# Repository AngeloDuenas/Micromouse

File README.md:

# Micromouse Robot Control PCB

A custom two-layer printed circuit board for a Micromouse robot, developed in KiCad. The hardware integrates an STM32-based controller, infrared wall sensing, dual DC motor control, encoder connections, and battery-powered voltage regulation for autonomous maze-navigation development.

This repository documents the electrical design and PCB implementation. Hardware validation and robot navigation performance are not claimed by the design files alone.

## Hardware Overview

| Subsystem | Implementation | Function |
| --- | --- | --- |
| Microcontroller | STM32F411RE on NUCLEO-F411RE | Central control and peripheral interfaces |
| Motor driver | L293D dual H-bridge | Drives two DC gearmotors |
| Motor feedback | Two 6-pin motor/encoder connectors | Interfaces to the gearmotor encoders |
| Wall sensing | 4 x INL-5AMIR15 IR emitters and 4 x SFH 313 FA receivers | Detects nearby maze walls |
| IR switching | 4 x BS170 MOSFETs | Controls the IR emitters |
| Voltage regulation | TPS62162DSG buck converter | Generates the 3.3 V supply rail |
| Power input | 2-pin battery connector and 500SSP1S2M2QEA switch | Connects and switches battery power |
| Debug interface | 4-pin SWD connector | Provides programming/debug signal access |

## System Block Diagram

```mermaid
flowchart TB
    BAT["Battery Input"] --> SW["Power Switch"]
    SW --> VBAT["Battery Supply (VBAT)"]
    VBAT --> REG["TPS62162DSG Buck Converter"]
    REG --> V33["3.3 V Supply"]
    V33 --> MCU["NUCLEO-F411RE / STM32F411RE"]
    V33 --> IR["4 Infrared Emitter / Receiver Channels"]
    VBAT --> DRV["L293D Dual H-Bridge"]
    MCU -->|"Motor control signals"| DRV
    DRV -->|"Motor output"| LEFT["Left DC Gearmotor"]
    DRV -->|"Motor output"| RIGHT["Right DC Gearmotor"]
    LEFT -->|"Encoder feedback"| MCU
    RIGHT -->|"Encoder feedback"| MCU
    MCU -->|"Emitter control"| IR
    IR -->|"Wall sensing feedback"| MCU
    SWD["SWD / Reset Header"] --- MCU
```

The battery rail supplies the motor driver and the buck regulator. The regulated 3.3 V rail serves the microcontroller and infrared sensing circuitry. The STM32 controls the two motors and receives encoder and infrared sensor signals for closed-loop navigation.

## Hardware Design

### Microcontroller and Debugging

The design uses an **ST NUCLEO-F411RE** board built around the **STM32F411RE** microcontroller. The controller interfaces with the wall sensors, motor driver, and motor encoders. A separate header exposes SWD and reset-related signals for debugging.

### Drive System

An **L293D** dual H-bridge controls two DC gearmotors. Each motor connects through a 6-pin interface that also accommodates encoder signals. The motor power path uses the battery supply, while control and feedback signals connect to the STM32.

### Infrared Wall Detection

Four sensing channels provide wall-detection inputs. Each channel combines an **INL-5AMIR15** infrared emitter, an **SFH 313 FA** infrared receiver, and a **BS170** MOSFET-based emitter control circuit. The microcontroller controls illumination and reads the corresponding sensor outputs.

### Power Distribution

A two-pin battery connector and mechanical power switch feed the **VBAT** net. The **TPS62162DSG** buck converter produces the **3.3 V** supply for the low-voltage electronics. Battery, regulator, and motor-driver requirements must be checked against the selected battery and motor operating conditions before assembly.

## PCB and Design Files

The PCB is designed as a **two-layer board** in **KiCad**. The project includes hierarchical schematic sheets, a PCB layout, imported component libraries and 3D models, a bill of materials, and existing fabrication outputs.

```text
.
├── team3_micromouse_202526_7F5.kicad_pro
├── team3_micromouse_202526_7F5.kicad_sch
├── team3_micromouse_202526_7F5.kicad_pcb
├── Microcontroller.kicad_sch
├── motors.kicad_sch
├── IR.kicad_sch
├── power_module.kicad_sch
├── team3_BOM_micromouse_202526_7F5.xlsx
├── imports/
├── gerber/
└── README.md
```

The `imports/` directory contains third-party symbols, footprints, and mechanical models. The `gerber/` directory contains previously generated fabrication files and should not be assumed to represent the latest schematic revision.

## Opening the Project

1. Install **KiCad 9** or a version compatible with the project files.
2. Open `team3_micromouse_202526_7F5.kicad_pro` in KiCad.
3. Review the hierarchical schematic and the PCB layout.
4. Resolve any local symbol, footprint, or 3D-model library paths if prompted.
5. Run electrical rules checking (ERC) and design rules checking (DRC) before generating new production files.

## Development Status

**Hardware design in progress.** The supplied archive contains PCB and schematic design files, but does not establish a completed, assembled, or validated robot. The schematic sheets have been revised more recently than the existing PCB and fabrication outputs; review their consistency before ordering boards.

Current engineering checks include supply-voltage compatibility, motor-driver and switch current ratings, regulator loading, encoder and sensor pin assignments, and board-level ERC/DRC results. Firmware and measured test results are not included in the supplied hardware archive.

## Project Attribution

Maintained by **Angelo Duenas**. Original design credits are retained in the schematic title blocks.

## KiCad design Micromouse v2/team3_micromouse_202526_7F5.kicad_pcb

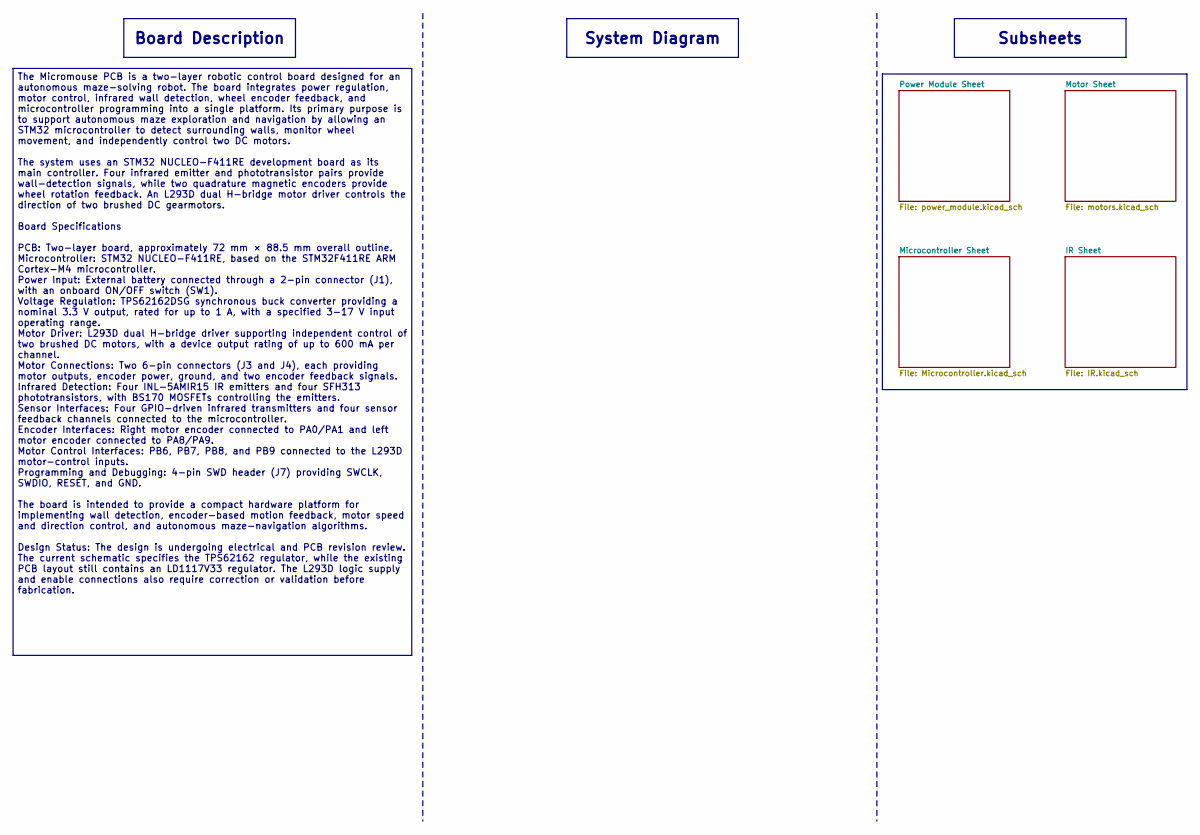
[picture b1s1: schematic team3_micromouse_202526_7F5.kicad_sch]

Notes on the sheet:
System Diagram
Board Description
The Micromouse PCB is a two-layer robotic control board designed for an autonomous maze-solving robot. The board integrates power regulation, motor control, infrared wall detection, wheel encoder feedback, and microcontroller programming into a single platform. Its primary purpose is to support aut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
Subsheets

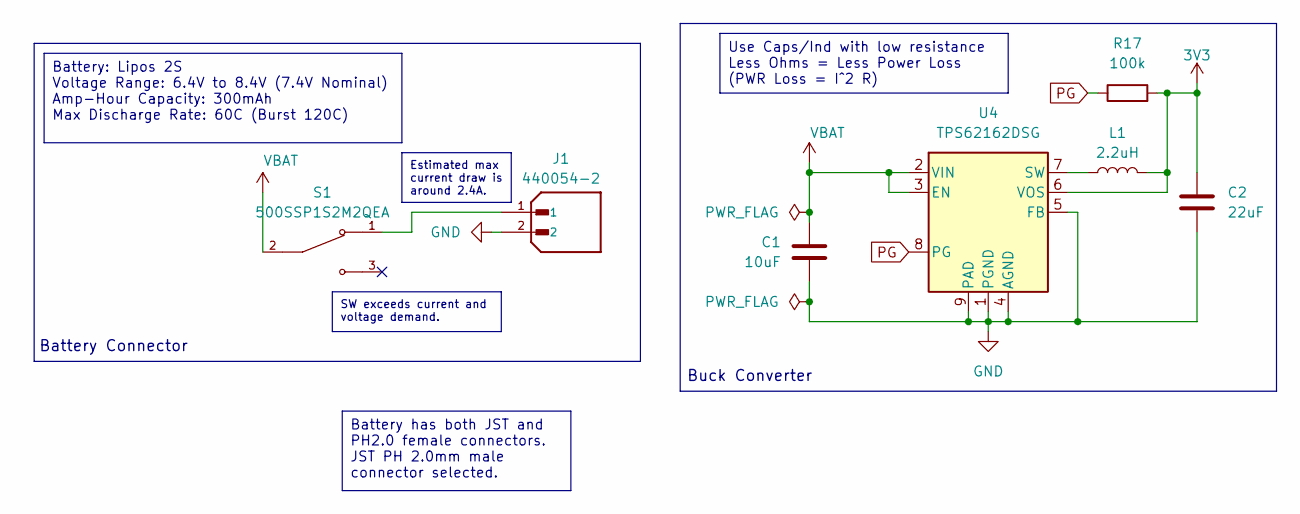
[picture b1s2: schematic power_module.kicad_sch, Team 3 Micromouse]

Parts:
C1: 10uF; CAP_C320_KEM
C2: 22uF; CAP_C320_KEM
J1: 440054-2; TE_440054-2_1x02_P2.00mm_Vertical; PARTREV F9
L1: 2.2uH; L_0603_1608Metric
R17: 100k; R_0603_1608Metric
S1: 500SSP1S2M2QEA; SW_500SSP1S2M2QEA; PARTREV C
U4: TPS62162DSG; WSON-8-1EP_2x2mm_P0.5mm_EP0.9x1.6mm_ThermalVias

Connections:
3V3: C2.1, L1.2, R17.2, U4.6 (VOS); also elsewhere on the board
GND: C1.2, C2.2, J1.2, U4.1 (PGND), U4.4 (AGND), U4.5 (FB), U4.9 (PAD); also elsewhere on the board
unnamed: J1.1, S1.1
unnamed: L1.1, U4.7 (SW)
PG: R17.1, U4.8 (PG)
VBAT: C1.1, S1.2, U4.2 (VIN), U4.3 (EN); also elsewhere on the board

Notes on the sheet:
Battery Connector
Buck Converter
Estimated max current draw is around 2.4A.
Use Caps/Ind with low resistance Less Ohms = Less Power Loss (PWR Loss = I^2 R)
Battery has both JST and PH2.0 female connectors. JST PH 2.0mm male connector selected.
SW exceeds current and voltage demand.
Battery: Lipos 2S Voltage Range: 6.4V to 8.4V (7.4V Nominal) Amp-Hour Capacity: 300mAh Max Discharge Rate: 60C (Burst 120C)

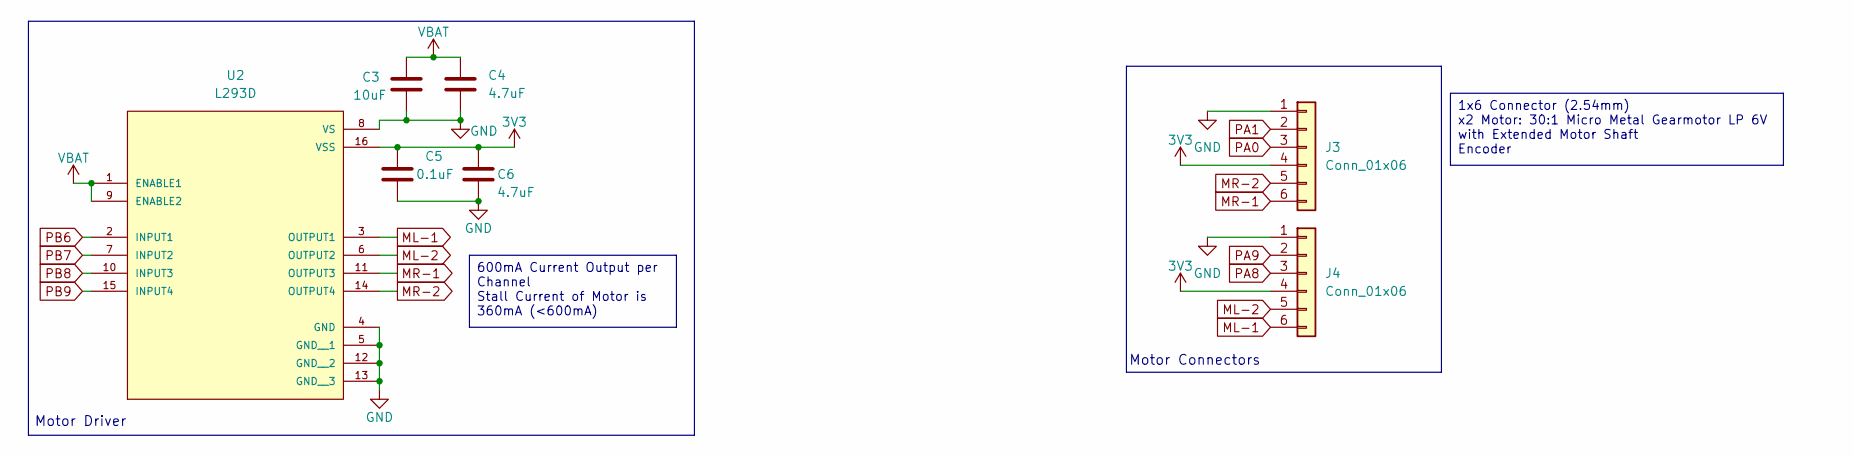
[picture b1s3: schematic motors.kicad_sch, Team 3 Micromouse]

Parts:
C3: 10uF; CAP_C320_KEM
C4, C6: 4.7uF; CAP_C320_KEM
C5: 0.1uF; CAP_C320_KEM
J3, J4: Conn_01x06; PinHeader_1x06_P2.54mm_Vertical
U2: L293D; DIP880W50P254L2000H510Q16

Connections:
3V3: C5.1, C6.1, J3.4, J4.4, U2.16 (VSS); also elsewhere on the board
GND: C3.2, C4.2, C5.2, C6.2, J3.1, J4.1, U2.4 (GND), U2.5 (GND__1), U2.8 (VS), U2.12 (GND__2), U2.13 (GND__3); also elsewhere on the board
ML-1: J4.6, U2.3 (OUTPUT1)
ML-2: J4.5, U2.6 (OUTPUT2)
MR-1: J3.6, U2.11 (OUTPUT3)
MR-2: J3.5, U2.14 (OUTPUT4)
PA0: J3.3; also elsewhere on the board
PA1: J3.2; also elsewhere on the board
PA8: J4.3; also elsewhere on the board
PA9: J4.2; also elsewhere on the board
PB6: U2.2 (INPUT1); also elsewhere on the board
PB7: U2.7 (INPUT2); also elsewhere on the board
PB8: U2.10 (INPUT3); also elsewhere on the board
PB9: U2.15 (INPUT4); also elsewhere on the board
VBAT: C3.1, C4.1, U2.1 (ENABLE1), U2.9 (ENABLE2); also elsewhere on the board

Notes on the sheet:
Motor Connectors
Motor Driver
1x6 Connector (2.54mm) x2 Motor: 30:1 Micro Metal Gearmotor LP 6V with Extended Motor Shaft Encoder
600mA Current Output per Channel Stall Current of Motor is 360mA (<600mA)

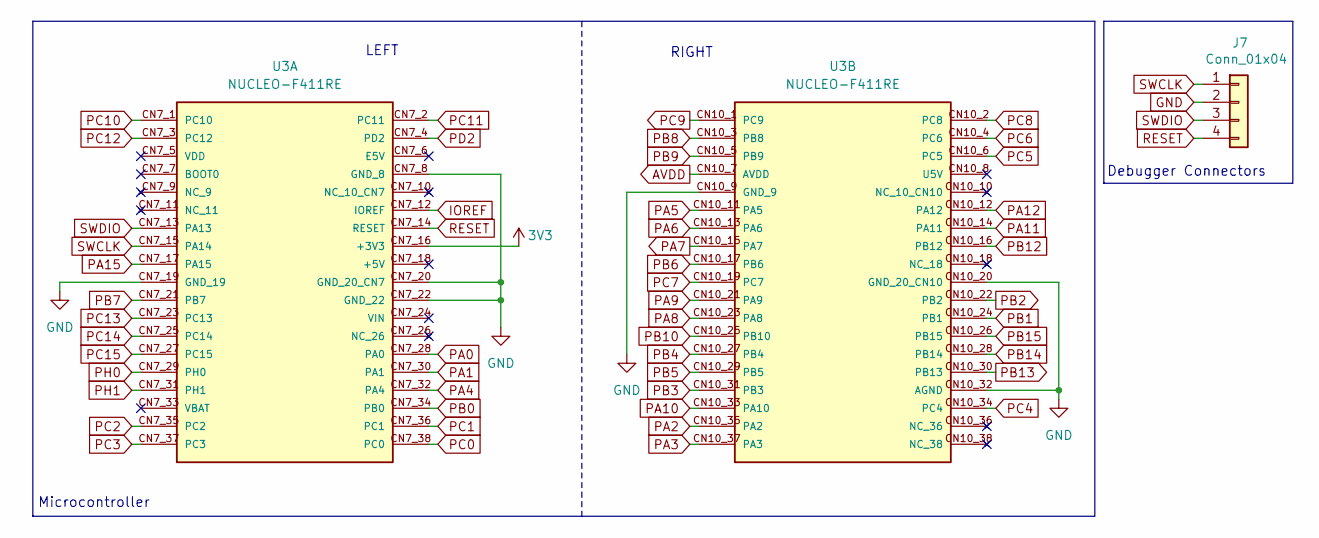
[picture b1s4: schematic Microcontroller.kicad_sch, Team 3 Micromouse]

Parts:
J7: Conn_01x04; PinSocket_1x04_P2.54mm_Vertical
U3: NUCLEO-F411RE; PARTREV 14; DigiKey_Part_Number 497-14711-ND

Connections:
3V3: U3.CN7_16 (+3V3); also elsewhere on the board
AVDD: U3.CN10_7 (AVDD)
GND: J7.2, U3.CN7_8 (GND_8), U3.CN7_19 (GND_19), U3.CN7_20 (GND_20_CN7), U3.CN7_22 (GND_22), U3.CN10_9 (GND_9), U3.CN10_20 (GND_20_CN10), U3.CN10_32 (AGND); also elsewhere on the board
IOREF: U3.CN7_12 (IOREF)
PA0: U3.CN7_28 (PA0); also elsewhere on the board
PA1: U3.CN7_30 (PA1); also elsewhere on the board
PA2: U3.CN10_35 (PA2)
PA3: U3.CN10_37 (PA3)
PA4: U3.CN7_32 (PA4)
PA5: U3.CN10_11 (PA5)
PA6: U3.CN10_13 (PA6); also elsewhere on the board
PA7: U3.CN10_15 (PA7); also elsewhere on the board
PA8: U3.CN10_23 (PA8); also elsewhere on the board
PA9: U3.CN10_21 (PA9); also elsewhere on the board
PA10: U3.CN10_33 (PA10)
PA11: U3.CN10_14 (PA11)
PA12: U3.CN10_12 (PA12)
PA15: U3.CN7_17 (PA15)
PB0: U3.CN7_34 (PB0)
PB1: U3.CN10_24 (PB1); also elsewhere on the board
PB2: U3.CN10_22 (PB2); also elsewhere on the board
PB3: U3.CN10_31 (PB3)
PB4: U3.CN10_27 (PB4)
PB5: U3.CN10_29 (PB5)
PB6: U3.CN10_17 (PB6); also elsewhere on the board
PB7: U3.CN7_21 (PB7); also elsewhere on the board
PB8: U3.CN10_3 (PB8); also elsewhere on the board
PB9: U3.CN10_5 (PB9); also elsewhere on the board
PB10: U3.CN10_25 (PB10)
PB12: U3.CN10_16 (PB12)
PB13: U3.CN10_30 (PB13); also elsewhere on the board
PB14: U3.CN10_28 (PB14)
PB15: U3.CN10_26 (PB15)
PC0: U3.CN7_38 (PC0)
PC1: U3.CN7_36 (PC1)
PC2: U3.CN7_35 (PC2)
PC3: U3.CN7_37 (PC3)
PC4: U3.CN10_34 (PC4); also elsewhere on the board
PC5: U3.CN10_6 (PC5); also elsewhere on the board
PC6: U3.CN10_4 (PC6)
PC7: U3.CN10_19 (PC7)
PC8: U3.CN10_2 (PC8)
PC9: U3.CN10_1 (PC9); also elsewhere on the board
PC10: U3.CN7_1 (PC10)
PC11: U3.CN7_2 (PC11)
PC12: U3.CN7_3 (PC12)
PC13: U3.CN7_23 (PC13)
PC14: U3.CN7_25 (PC14)
PC15: U3.CN7_27 (PC15)
PD2: U3.CN7_4 (PD2)
PH0: U3.CN7_29 (PH0)
PH1: U3.CN7_31 (PH1)
RESET: J7.4, U3.CN7_14 (RESET)
SWCLK: J7.1, U3.CN7_15 (PA14)
SWDIO: J7.3, U3.CN7_13 (PA13)

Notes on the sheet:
Debugger Connectors
Microcontroller
RIGHT
LEFT

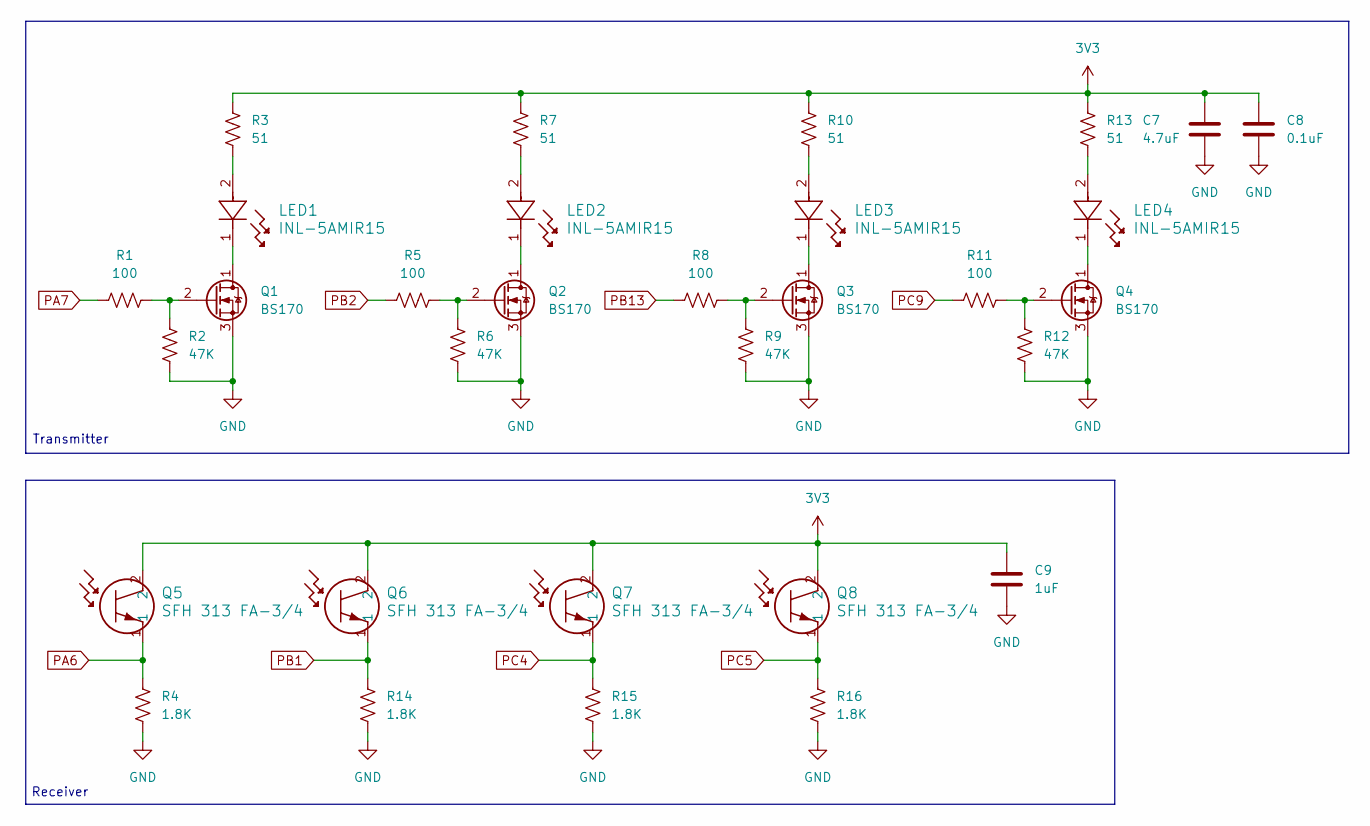
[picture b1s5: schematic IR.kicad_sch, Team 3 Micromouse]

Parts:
C7: 4.7uF; CAP_C320_KEM
C8: 0.1uF; CAP_C320_KEM
C9: 1uF; CAP_C320_KEM
LED1, LED2, LED3, LED4: INL-5AMIR15; LED_INL-5AMIR15_INO
Q1, Q2, Q3, Q4: BS170; TO-92_Inline
Q5, Q6, Q7, Q8: SFH 313 FA-3/4; SFH 313 FA-3&slash_4_OSR
R1, R5, R8, R11: 100; R_Axial_DIN0204_L3.6mm_D1.6mm_P1.90mm_Vertical
R2, R6, R9, R12: 47K; R_Axial_DIN0204_L3.6mm_D1.6mm_P1.90mm_Vertical
R3, R7, R10, R13: 51; R_Axial_DIN0204_L3.6mm_D1.6mm_P1.90mm_Vertical
R4, R14, R15, R16: 1.8K; R_Axial_DIN0204_L3.6mm_D1.6mm_P1.90mm_Vertical

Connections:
3V3: C7.1, C8.1, C9.1, Q5.2, Q6.2, Q7.2, Q8.2, R3.2, R7.2, R10.2, R13.2; also elsewhere on the board
GND: C7.2, C8.2, C9.2, Q1.3 (S), Q2.3 (S), Q3.3 (S), Q4.3 (S), R2.1, R4.1, R6.1, R9.1, R12.1, R14.1, R15.1, R16.1; also elsewhere on the board
unnamed: LED1.2, R3.1
unnamed: LED2.2, R7.1
unnamed: LED3.2, R10.1
unnamed: LED4.2, R13.1
unnamed: LED1.1, Q1.1 (D)
unnamed: Q1.2 (G), R1.2, R2.2
unnamed: LED2.1, Q2.1 (D)
unnamed: Q2.2 (G), R5.2, R6.2
unnamed: LED3.1, Q3.1 (D)
unnamed: Q3.2 (G), R8.2, R9.2
unnamed: LED4.1, Q4.1 (D)
unnamed: Q4.2 (G), R11.2, R12.2
PA6: Q5.1, R4.2; also elsewhere on the board
PA7: R1.1; also elsewhere on the board
PB1: Q6.1, R14.2; also elsewhere on the board
PB2: R5.1; also elsewhere on the board
PB13: R8.1; also elsewhere on the board
PC4: Q7.1, R15.2; also elsewhere on the board
PC5: Q8.1, R16.2; also elsewhere on the board
PC9: R11.1; also elsewhere on the board

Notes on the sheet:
Transmitter
Receiver

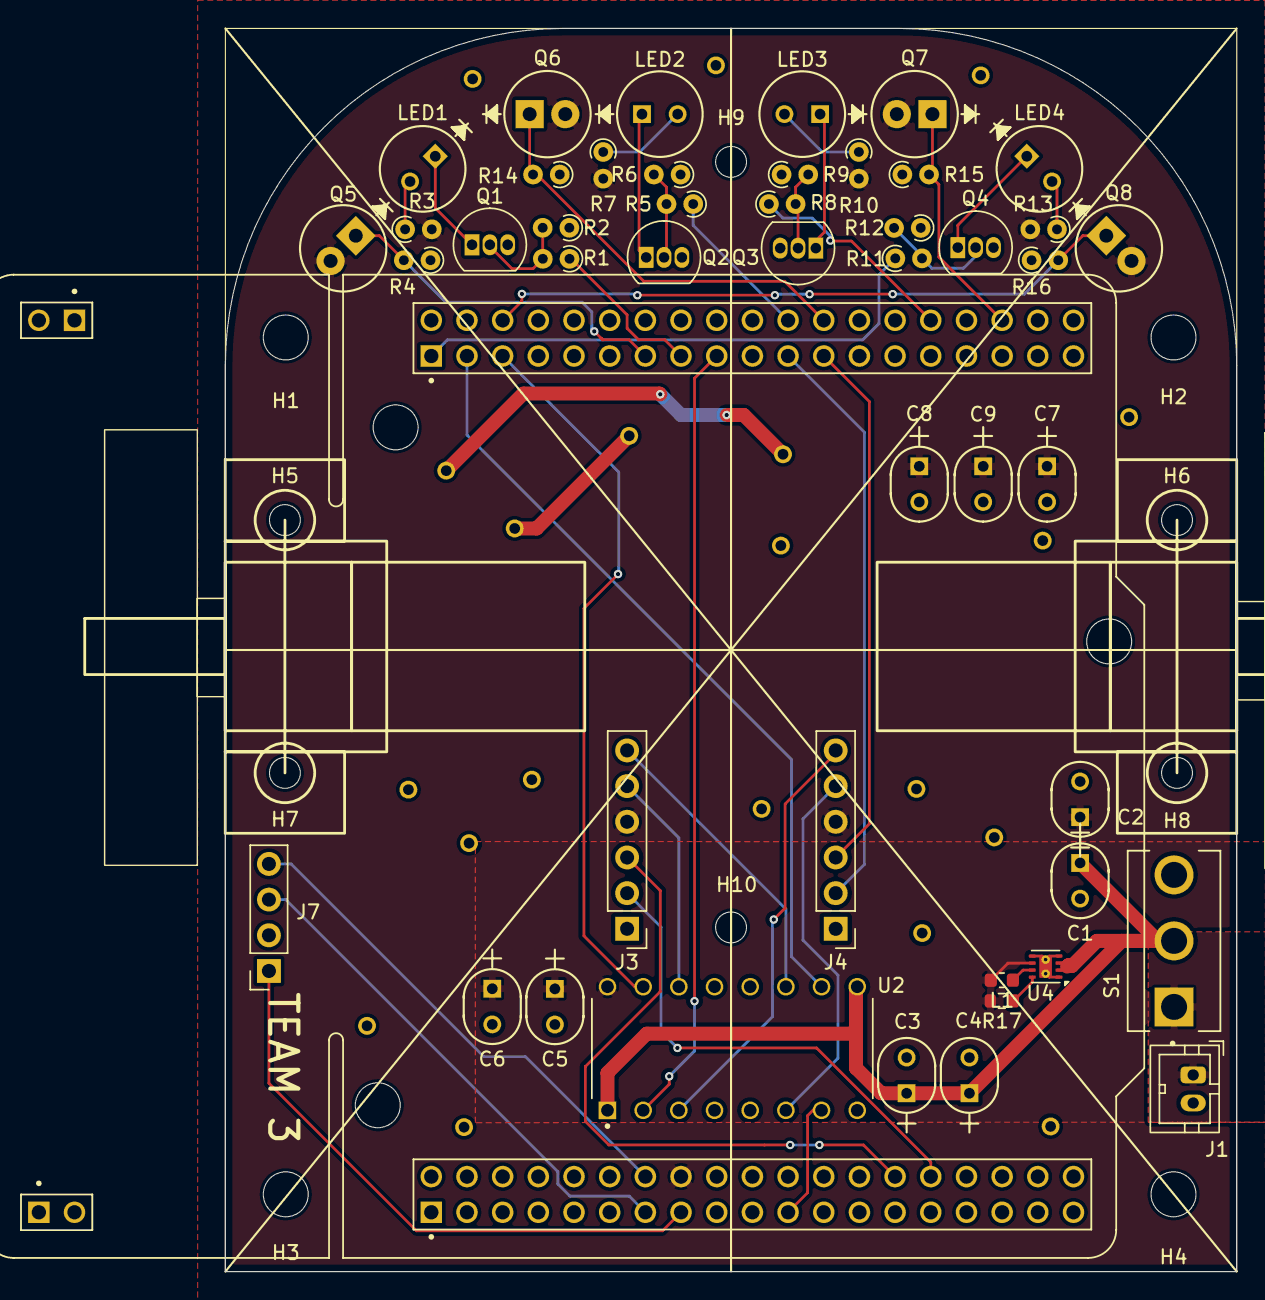
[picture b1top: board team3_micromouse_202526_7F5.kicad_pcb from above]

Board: 2 copper layers, 72.0 x 88.5 mm, 57 parts (0 on the bottom side), 41 nets.

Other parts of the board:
H1, H2, H3, H4: MountingHole_3.2mm_M3
H5, H6, H7, H8: MountingHole_2.2mm_#2-56; MountingHole_2.2mm_M2
H9, H10: MountingHole_2.2mm_M2

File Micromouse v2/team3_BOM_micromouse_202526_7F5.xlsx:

Price | Qty | Value | Datasheet | Digikey | Reference | Description | Tag
0.1 | 1 | 440054-2 | https://www.te.com/usa-en/product-440054-2.datasheet.pdf | https://www.digikey.com/en/products/detail/te-connectivity-a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 | J1 | Connector Header Through Hole 2 position 0.079" (2.00mm) | 2
3.56 | 4 | INL-5AMIR15 | https://www.inolux-corp.com/datasheet/IR/Emitter/5mm%20Lamp/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 | https://www.digikey.com/en/products/detail/inolux/INL-5AMIR1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 | LED1,LED2,LED3,LED4 | Infrared (IR) Emitter 880nm 1.3V 100mA 7.8mW/sr @ 20mA 15° Radial | 2
1.72 | 4 | BS170 | https://www.onsemi.com/pub/Collateral/BS170-D.PDF | https://www.digikey.com/en/products/detail/onsemi/BS170/244280 | Q1,Q2,Q3,Q4 | N-Channel 60 V 500mA (Ta) 830mW (Ta) Through Hole TO-92-3 | 2
3.2 | 4 | SFH 313 FA-3/4 | https://look.ams-osram.com/m/5f84917e436bcd12/original/SFH-3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 | https://www.digikey.com/en/products/detail/ams-osram-usa-inc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 | Q5,Q6,Q7,Q8 | Phototransistors 870nm Top View Radial | 2
0.72 | 1 | EG1218 | https://configured-product-images.s3.amazonaws.com/Datasheet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 | https://www.digikey.com/en/products/detail/e-switch/EG1218/101726 | SW1 | Slide Switch SPDT Through Hole | 2
0.57 | 1 | LD1117V33 | https://www.st.com/content/ccc/resource/technical/document/d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 | https://www.digikey.com/en/products/detail/stmicroelectronic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 | U1 | Linear Voltage Regulator IC Positive Fixed 1 Output 800mA TO-220 | 2
8.86 | 1 | L293D | https://www.st.com/content/ccc/resource/technical/document/d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 | https://www.digikey.com/en/products/detail/stmicroelectronic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 | U2 | Bipolar Motor Driver Parallel 16-PowerDIP | 2
1.74 | 2 | BM06B-SRSS-TBT | https://www.jst-mfg.com/product/pdf/eng/eSR_SZ.pdf | https://www.digikey.com/en/products/detail/jst-sales-america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 | J3,J4 | Connector Header Surface Mount 6 position 0.039" (1.00mm) | 0
7.18 | 2 | PinSocket_2x19_P2.54mm_Vertical | https://www.pololu.com/product/3676/specs | https://www.pololu.com/product/3676 | J5,J6 | Stackable 0.100″ Female Header for TI-RSLK MAX: 2x19-Pin, Straight | 0
9.5 | 2 | PinSocket_2x20_P2.54mm_Vertical | https://www.pololu.com/product/2748/specs | https://www.pololu.com/product/2748 | ~ | This stackable 40-pin female header features two rows of 20 pins spaced with a 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 | 0
0.79 | 1 | PinHeader_1x04_P2.54mm_Vertical_SMD_Pin1Left | https://www.pololu.com/product/1014/specs | https://www.pololu.com/product/1014 | J7 | 0.100" (2.54 mm) Female Header: 1x4-Pin, Straight | 0
59.9 | 2 | 30:1 Micro Metal Gearmotor MP 6V with 12 CPR Encoder, Back Connector | https://www.pololu.com/file/0J1487/pololu-micro-metal-gearmo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 | https://www.pololu.com/product/5132 | ~ | MP 6V: medium-power 6V with precious metal brushes, 9.86:1 with brass plates , 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 | 3
2.95 | 1 | Pololu Micro Metal Gearmotor Bracket Pair – White | https://www.pololu.com/product/1086/specs | https://www.pololu.com/product/1086 | ~ | These plastic mounting brackets allow you to easily and securely mount the ubiq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 | 3
4.45 | 1 | Pololu Wheel 32×7mm Pair - White | https://www.pololu.com/product/1088/specs | https://www.pololu.com/product/1088/ | ~ | These white plastic wheels have silicone tires and measure 32 mm (1.26″) in dia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 | 3
7.22 | 2 | JST SH-Style Cable, 6-Pin, Female-Female, 16cm | https://www.pololu.com/product/5544/specs | https://www.pololu.com/product/5544 | ~ | This 6-conductor, 16 cm (6.3″) cable has 28 AWG wires and 6-pin female JST SH-t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 | 3
13.82 | 1 | NUCLEO-F411RE | https://www.st.com/content/ccc/resource/technical/document/d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 | https://www.digikey.com/en/products/detail/stmicroelectronic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 | ~ | STM32F411RE Nucleo-64 STM32F4 ARM® Cortex®-M4 MCU 32-Bit Embedded Evaluation Bo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 | 1
0 | 4 | 47KΩ | ~ | ~ | R2,R6,R9,R12 | 47KΩ±1% 1/4W Metal Film Resistor Axial | 0
0 | 4 | 51Ω | ~ | ~ | R3,R7,R10,R13 | 51Ω±1% 1/4W Metal Film Resistor Axial | 0
0 | 4 | 100Ω | ~ | ~ | R1,R5,R8,R11 | 100Ω±1% 1/4W Metal Film Resistor Axial | 0
0 | 4 | 1.8KΩ | ~ | ~ | R4,R14,R15,R16 | 1.8KΩ±1% 1/4W Metal Film Resistor Axial | 0
0 | 3 | 0.1uF | ~ | ~ | C1,C5,C8 | 0.1µF ±10% 50V Multilayer Ceramic Capacitor Radial | 0
0 | 1 | 1uF | ~ | ~ | C9 | 1.0µF ±10% 50V Multilayer Ceramic Capacitor Radial | 0
0 | 3 | 4.7uF | ~ | ~ | C4,C6,C7 | 4.7µF ±10% 25V Multilayer Ceramic Capacitor Radial | 0
0 | 2 | 10uF | ~ | ~ | C2,C3 | 10µF ±10% 25V Multilayer Ceramic Capacitor Radial | 0
0 | 1 | Battery | ~ | ~ | ~ | ~ | 1
126.28 | 56 | Budget | ~ | ~ | ~ | Team 3 Micromouse 2026 Budget | -1
